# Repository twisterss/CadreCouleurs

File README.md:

# Decorative LED frame

## More info

Find details about the way to [build the frame yourself here](http://www.viesurip.fr/en/2014/06/17/un-cadre-en-couleurs/).

## Repository structure

  * The "cadre" directory contains the Arduino sketch to control the display;
  * The "elec" directory contains the schematic of the control part of the frame;
  * The "things" directory contains the models to 3D-print or laser-cut to modify the frame;
  * The "tools" directory contains various tools useful to modify the frame.

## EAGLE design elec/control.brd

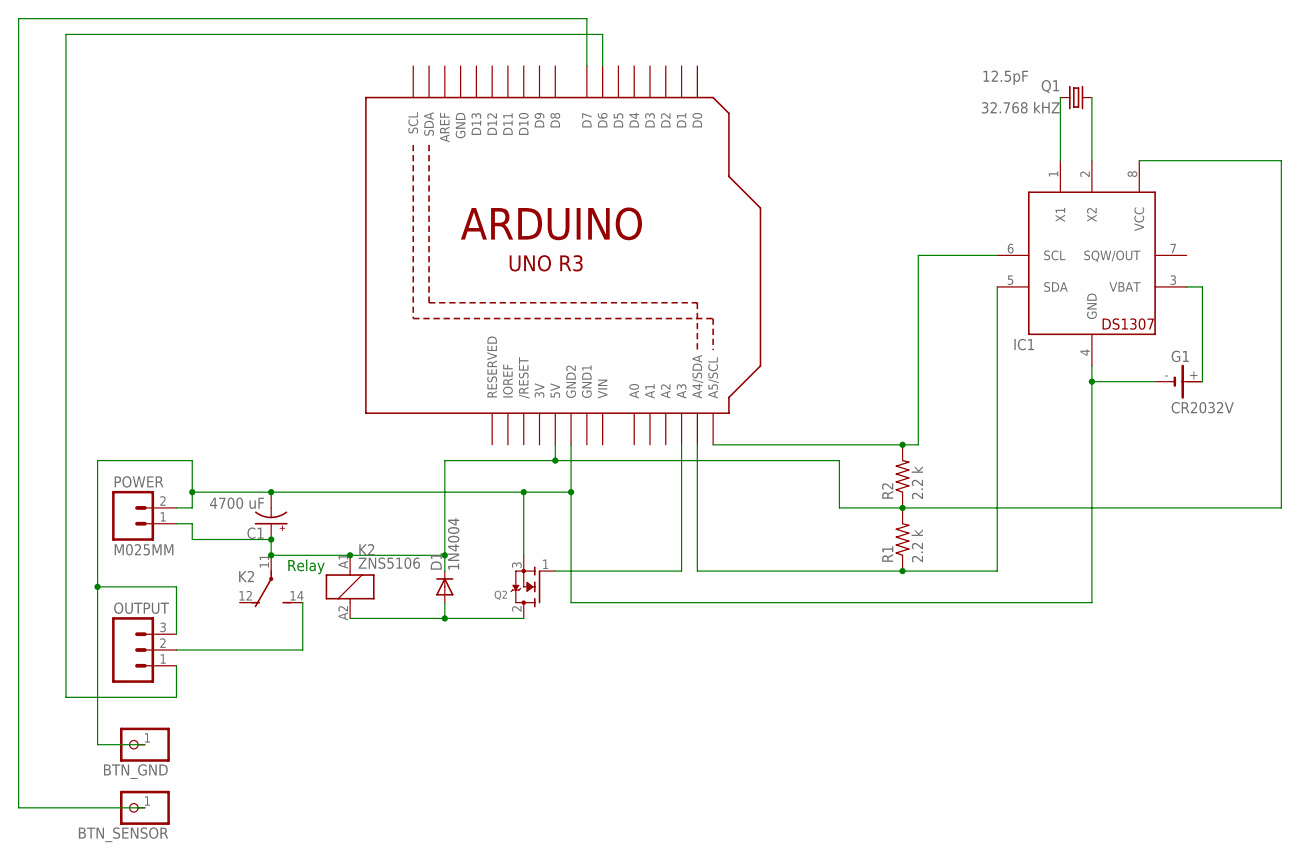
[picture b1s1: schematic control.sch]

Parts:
BTN_GND: PINHD-1X1CB; 1X01-CLEANBIG
BTN_SENSOR: PINHD-1X1CB; 1X01-CLEANBIG
C1: 4700 uF; E5-10,5
D1: 1N4004; DO41-10
G1: CR2032V
IC1: DS1307; DIL08
K2: ZNS5106; ZN5
OUTPUT: M03-SCREW-5MM; SCREWTERMINAL-5MM-3
POWER: M025MM; SCREWTERMINAL-5MM-2
Q1: 32.768 kHZ; TC38H
Q2: MOSFET-NGDS_TO220V; TO220V
R1, R2: 2.2 k; 0207/10
U1: ARDUINOR3-BPLACE

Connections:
3V: U1.3V
GND: U1.GND
GND1: U1.GND1
unnamed: BTN_GND.1, C1.-, G1.-, IC1.4 (GND), OUTPUT.3, POWER.2, Q2.3 (S), U1.GND2
unnamed: IC1.1 (X1), Q1.2
unnamed: Q2.1 (G), U1.A3
unnamed: D1.A, K2.A2 (2), Q2.2 (D)
unnamed: K2.14 (S), OUTPUT.2
unnamed: OUTPUT.1, U1.D6
unnamed: BTN_SENSOR.1, U1.D7
unnamed: IC1.2 (X2), Q1.1
unnamed: G1.+, IC1.3 (VBAT)
unnamed: IC1.6 (SCL), R2.2, U1.A5 (A5/SCL)
unnamed: IC1.5 (SDA), R1.1, U1.A4 (A4/SDA)
unnamed: C1.+, D1.C, IC1.8 (VCC), K2.11, K2.A1 (1), POWER.1, R1.2, R2.1, U1.5V
VIN: U1.VIN

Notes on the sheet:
Relay

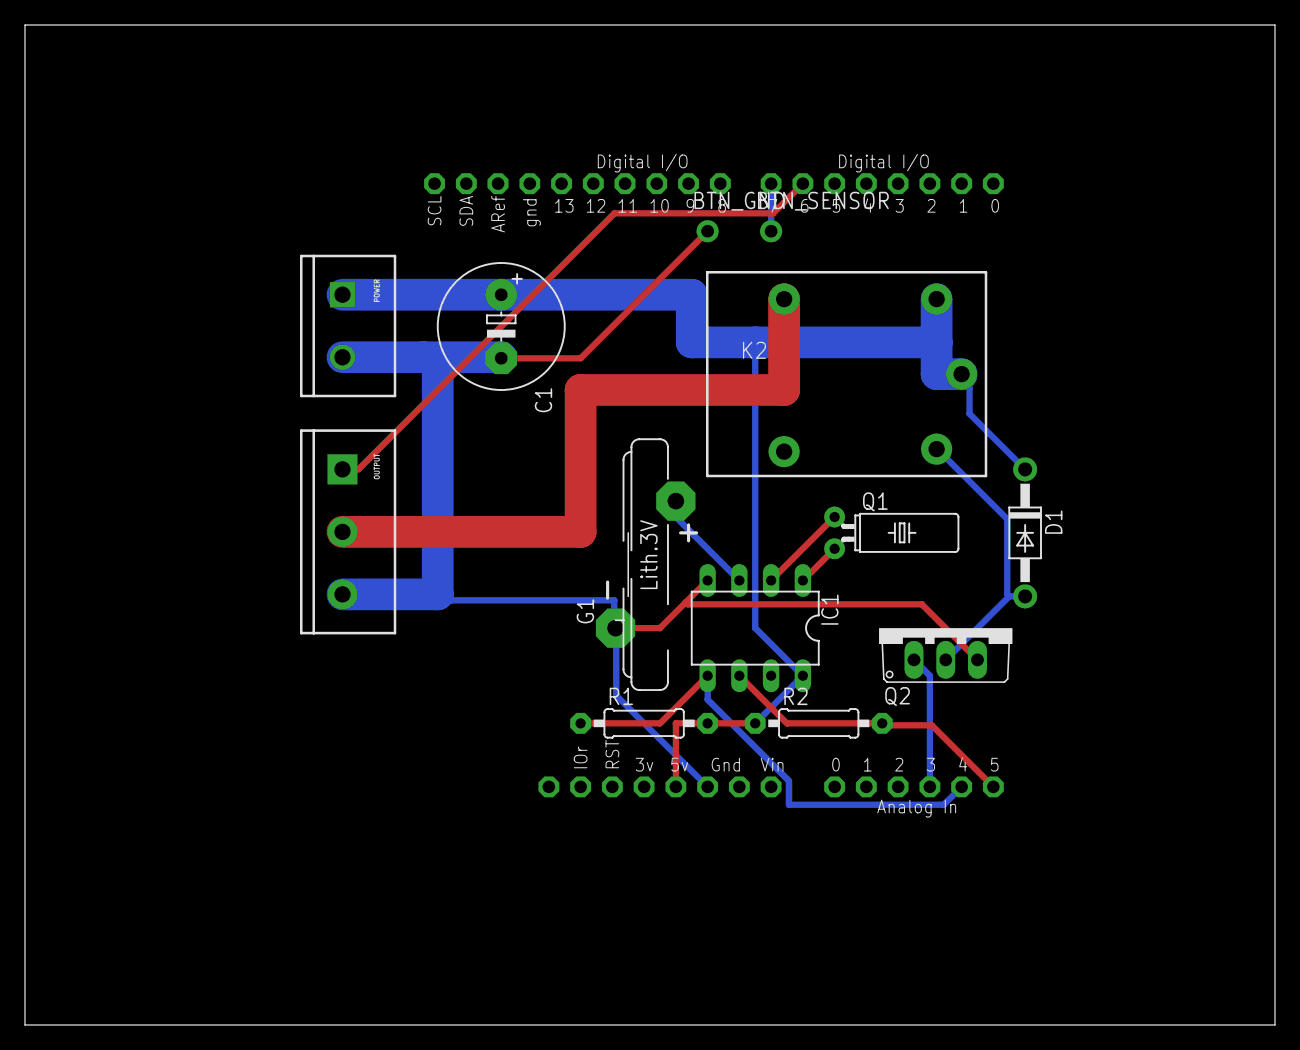
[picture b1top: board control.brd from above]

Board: 2 copper layers, 100.0 x 80.0 mm, 14 parts (0 on the bottom side), 12 nets.

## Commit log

2014-06-06 Initial commit
    The code works. First version with basic features.
2014-06-07 Improved a bit
    Made the web app work offline and look better in landscape mode.
    Removed the geometry mode and added a crazy light mode.
2014-06-07 Made random mode default
    Skipped showing the IP address if not connected.
2014-06-09 Added a watchdog and cleaned up
    Distance calculation for colors is a bit better.
    IP address display time is as short as possible.
    Removed useless features in Pixels.
2014-06-15 Added an RTC chip for time and state keeping
    Uses the RTC module to keep the time, as well as to keep the last state
    of the display.
2014-06-16 Added a demo mode
    This is the default mode when not connected. It cycles through some of
    the other modes.
2014-06-16 Added a button to display the IP address
    Also added the possibility to skip network connection when booting with
    button pressed.
    The box containing the Arduino has been modified to include the new
    plug and button.
2014-06-26 Added the ability to power off the strip
    This is done using a 5V relay that cuts the power wire of the strip.
2014-06-26 Updated the schematic to add the relay
2014-07-04 Added an alarm mode
    Also changed the random mode to be a bit smarter.
2014-07-18 Improved random colors, added rainbow mode
    Random colors are now loaded from the EEPROM, generated first by a
    python script.
    A rainbow mode allows to show changing colors.
2014-07-30 Added a version of the grid for laser cutting
    The SVG file is generated by a Python script ensuring accuracy.
2014-08-15 Added the ability to print the frame in one part
2014-08-16 Modified the alarm mode, added brightness settings
    The alarm mode now alternates between the time and a random color.
    Brightness settings are available for all random modes.
2014-10-14 Fixed a problem with browsers with color element
2014-10-19 Fixed a bug in Safari when changing color
2014-10-19 Forgotten manifest change
2014-10-19 Quick fix
2014-10-19 Small improvement for color changes
2014-10-20 Wait for connection if the button is not pushed
    At startup, the button has to be pushed immediately for the demo mode
    to start. Otherwise the frame will wait for the connection forever and
    keep retrying.
2014-10-24 Improvements: removed alarm, added smileys
    The alarm mode was never used.
    Added smileys to the text mode.
    Added the ability to change the demo text.
2014-11-02 Use Eagle instead of Fritzing for control
2014-11-02 Made the box bigger for easier Arduino insertion

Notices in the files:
parts and their libraries:
SparkFun-Connectors: Licensing: Creative Commons ShareAlike 4.0 International - https://creativecommons.org/licenses/by-sa/4.0
